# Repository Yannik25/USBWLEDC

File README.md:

# USBWLEDC
USB Sound Reactive WLED Controller

## Features

- USB-C for flashing and power (max. 3A)
- Small size (30mm x 35mm)
- Cheap components
- GSA4737 MEMS Microphone (similar to SPM1423)
- Solder Pads instead of Screw Terminal Blocks
- Files for panelized version (4x4)
- Files for 3D printed case
- Front side can be populated by JLCPCB

## Case

## Entering Flash Mode

To enter the Flash mode of the USBWLEDC, simply hold down the button as you connect the USB cable to a computer.

\* Update: With Rev. 1.2, CH340C has auto reset functionality, there should be no need to press the button during connection. 

## WLED Config

| Name | Value |
|------|-------|
| LED Output 1: GPIO | 32 |
| LED Output 2: GPIO | 33 |
| Button 0: GPIO | 0 |
| Digitalmic: Type | Generic I2S PDM |
| Digitalmic: Pin I2S SD | GPIO 23 |
| Digitalmic: Pin I2S WS | GPIO 22 |

## BOM

|Designators   |Footprint                                       |Quantity|Value                  |LCSC Part #|
|--------------|------------------------------------------------|--------|-----------------------|-----------|
|C1*, C2, C4, C9, C10 |Capacitor_SMD:C_0402_1005Metric                           |5    |100nF                  |C1525  |
|C3, C5, C7 |Capacitor_SMD:C_0603_1608Metric                           |3    |10uF                   |C96446  |
|C6         |Capacitor_SMD:C_0402_1005Metric                           |1    |1uF                    |C52923  |
|C8         |Capacitor_SMD:CP_Elec_5x5.4                               |1    |100uF                  |C7469983 |
|J10        |Connector_USB:USB_C_Receptacle_G-Switch_GT-USB-7010ASV    |1    |USB-C Receptacle       |C2988369|
|MK1*       |Microphone:Microphone-6pin                                |1    |ICS-43434 MEMS Microphone|C5656610|
|R1*        |Resistor_SMD:R_0402_1005Metric                            |1    |100k                   |C25741  |
|R2, R3, R6, R7    |Resistor_SMD:R_0402_1005Metric                            |4    |10k                    |C25531  |
|R4, R5     |Resistor_SMD:R_0603_1608Metric                            |2    |5.1k                   |C23186  |
|SW1        |Button_Switch_SMD:SW_Push_1P1T_XKB_TS-1187A               |1    |Push Button Flash      |C318884 |
|U2         |Package_TO_SOT_SMD:SOT-223-3_TabPin2                      |1    |AMS1117-3.3            |C6186   |
|U3**       |RF_Module:ESP32-WROOM-32E                                  |1    |ESP32-WROOM-32E         |C701341 |
|U4 		|Package_SO:VSSOP-8_2.3x2mm_P0.5mm			|1 		|SN74LVC2T45DCUR 		|C15741 |
|U5 		|Package_SO:SOIC-16_3.9x9.9mm_P1.27mm		|1 		|CH340C 				|C84681  |
|Q1, Q2       |Package_TO_SOT_SMD:SOT-23                                |2    |L8050QLT1G        |C49581 |
|D1       |Package_TO_SOT_SMD:SOT-143                               |1    |SP0503BAHT        |C2682275 |

\* You can build it without the microphone. Then you don't need R1, C1 and MK1.

\*\* The ESP32-WROOM Module can be purchased at a lower cost on AliExpress.

## Assembly

When ordering from JLCPCB, you have the option to get the front side of the board pre-populated - A service I strongly endorse. Subsequently, you'll only need to solder the ESP32-WROOM module onto the reverse side. With sufficient flux, this task can be accomplished with relative ease.

For those looking to populate the whole board, I suggest using a hot plate or a reflow oven for the front side.

    Be careful to keep Isopropyl Alcohol away from the hole of the microphone when cleaning the board!

## Disclaimer

The circuit board provided on this GitHub repository is offered "as is," without any warranties or guarantees of any kind. By accessing and utilizing this circuit board, you acknowledge and agree that you do so at your own risk.

The creator and contributor of this repository, shall not be held responsible or liable for any damages, losses, or injuries that may occur as a result of building and / or using this circuit board. This includes but is not limited to any direct, indirect, consequential, or incidental damages.

Electricity is dangerous. Only attempt this project if you know what you're doing.

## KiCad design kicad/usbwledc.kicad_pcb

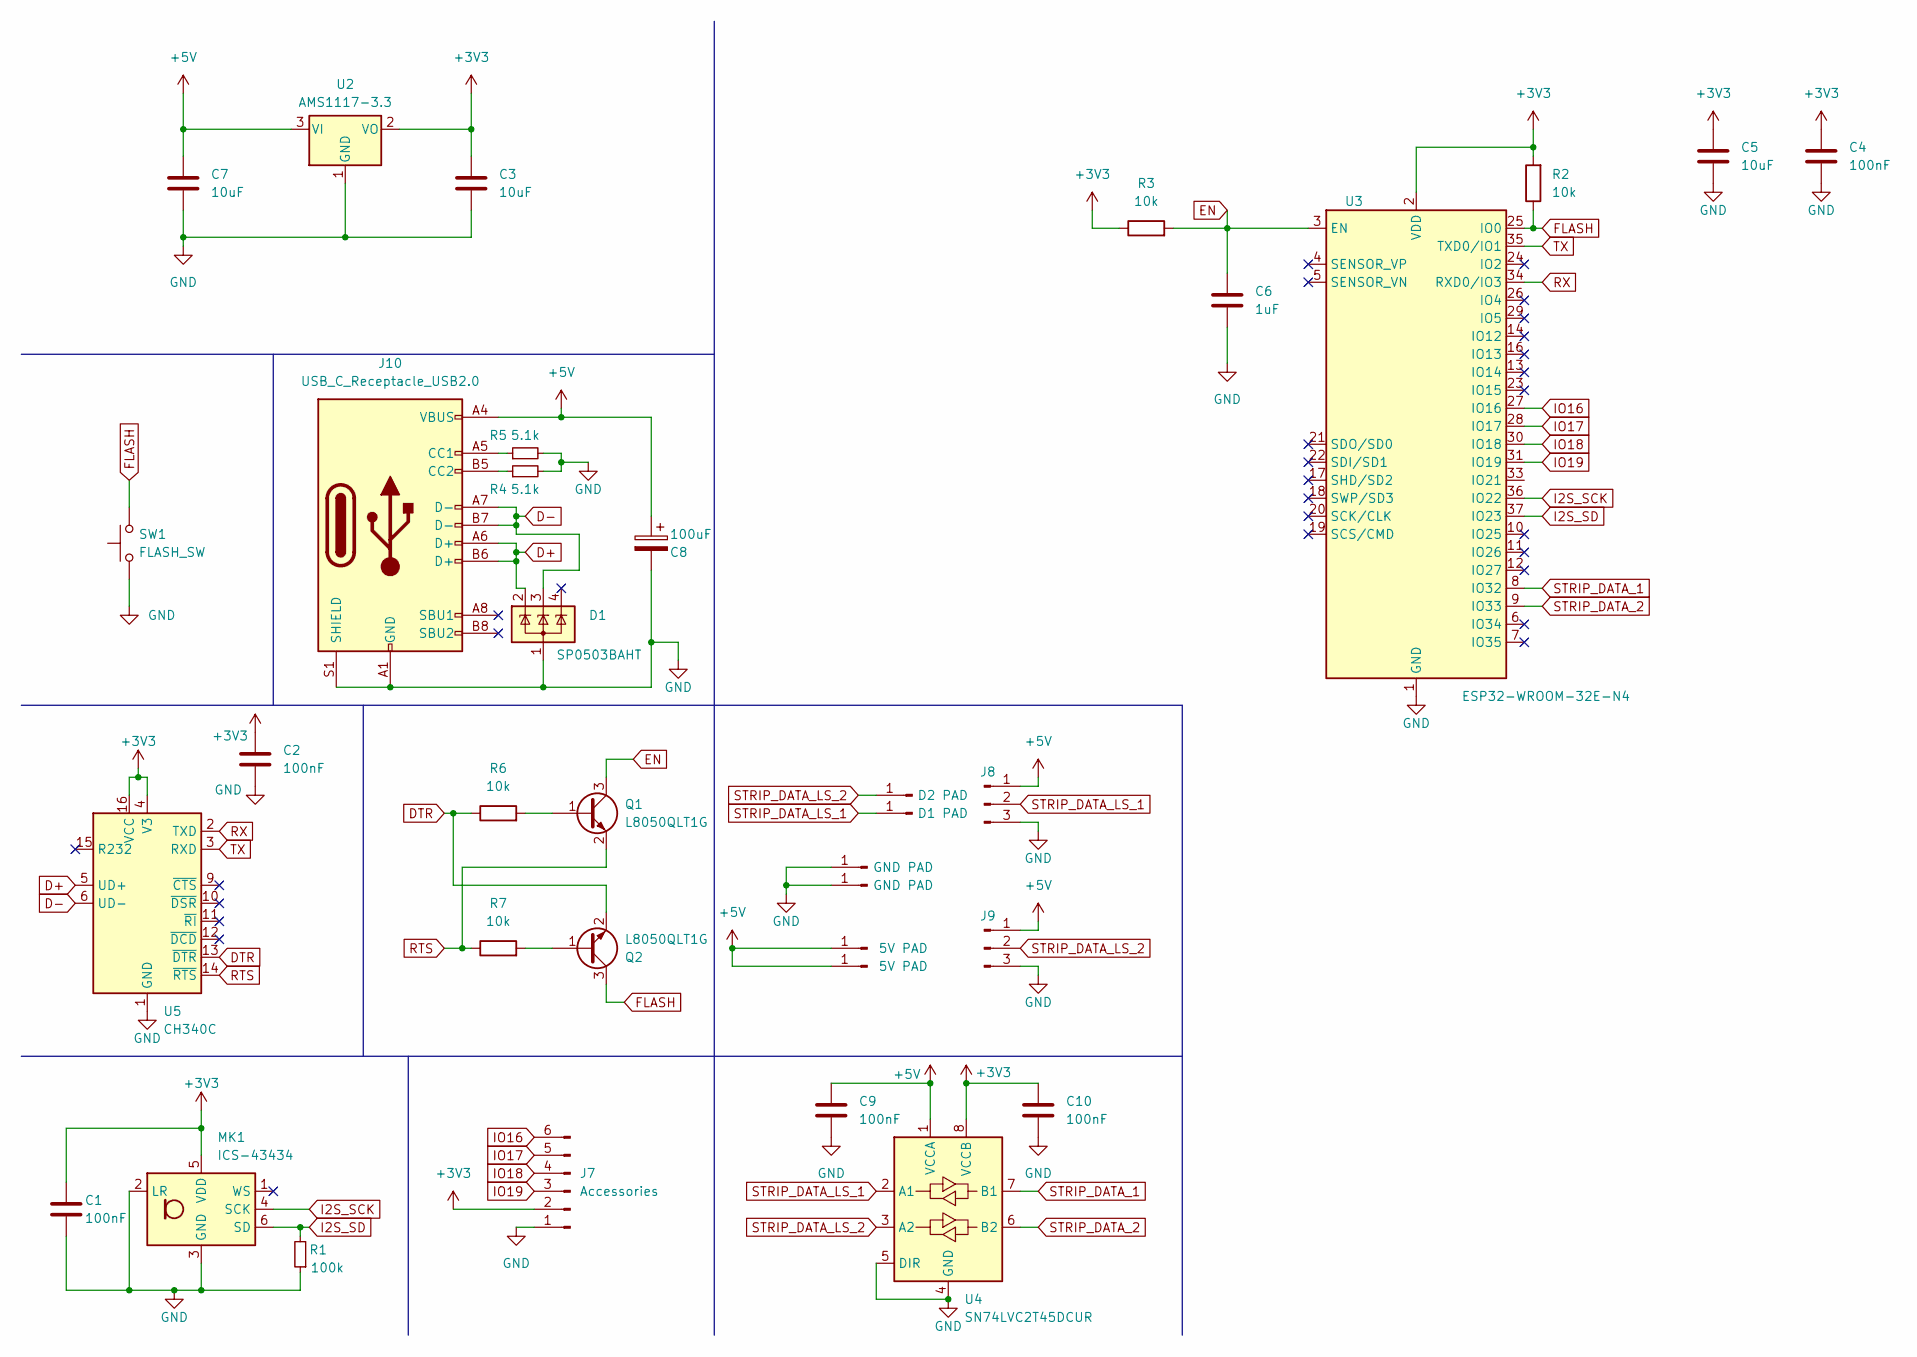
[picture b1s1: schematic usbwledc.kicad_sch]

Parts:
C1, C2, C4, C9, C10: 100nF; C_0402_1005Metric; MPN C1525; LCSC C1525
C3, C5, C7: 10uF; C_0603_1608Metric; MPN C96446; LCSC C96446
C6: 1uF; C_0402_1005Metric; MPN C52923; LCSC C52923
C8: 100uF; CP_Elec_5x5.4; MPN C7469983; LCSC C7469983
D1: SP0503BAHT; SOT-143; MPN C2682275; LCSC C2682275
J1, J4: 5V PAD; SolderWirePad_1x01_SMD_3x6mm
J2: D1 PAD; SolderWirePad_1x01_SMD_3x6mm
J3, J6: GND PAD; SolderWirePad_1x01_SMD_3x6mm
J5: D2 PAD; SolderWirePad_1x01_SMD_3x6mm
J7: Accessories; PinHeader_1x06_P2.54mm_Vertical
J8, J9: Conn_01x03_Pin; PinHeader_1x03_P2.54mm_Vertical
J10: USB_C_Receptacle_USB2.0; USB_C_Receptacle_G-Switch_GT-USB-7010ASV; MPN C2988369; LCSC C2988369
MK1: ICS-43434; InvenSense_ICS-43434-6_3.5x2.65mm; LCSC C5656610
Q1, Q2: L8050QLT1G; SOT-23; MPN C49581; LCSC C49581
R1: 100k; R_0402_1005Metric; MPN C25741; LCSC C25741
R2, R3, R6, R7: 10k; R_0402_1005Metric; MPN C25531; LCSC C25531
R4, R5: 5.1k; R_0603_1608Metric; MPN C23186; LCSC C23186
SW1: FLASH_SW; SW_Push_1P1T_XKB_TS-1187A; MPN C318884; LCSC C318884
U2: AMS1117-3.3; SOT-223-3_TabPin2; MPN C6186; LCSC C6186
U3: ESP32-WROOM-32E-N4; ESP32-WROOM-32E; MPN C701341; LCSC C701341
U4: SN74LVC2T45DCUR; VSSOP-8_2.3x2mm_P0.5mm; LCSC C15741
U5: CH340C; SOIC-16_3.9x9.9mm_P1.27mm; LCSC C84681

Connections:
+3V3: C1.1, C2.2, C3.1, C4.2, C5.1, C10.1, J7.2, MK1.5 (VDD), R2.2, R3.1, U2.2 (VO), U3.2 (VDD), U4.8 (VCCB), U5.4 (V3), U5.16 (VCC)
+5V: C7.1, C8.1, C9.1, J1.1, J4.1, J8.1, J9.1, J10.A4 (VBUS), J10.A9 (VBUS), J10.B4 (VBUS), J10.B9 (VBUS), U2.3 (VI), U4.1 (VCCA)
D+: D1.2 (K), J10.A6 (D+), J10.B6 (D+), U5.5 (UD+)
D-: D1.3 (K), J10.A7 (D-), J10.B7 (D-), U5.6 (UD-)
DTR: Q2.2 (E), R6.1, U5.13 (~DTR)
EN: C6.1, Q1.3 (C), R3.2, U3.3 (EN)
FLASH: Q2.3 (C), R2.1, SW1.2, U3.25 (IO0)
GND: C1.2, C2.1, C3.2, C4.1, C5.2, C6.2, C7.2, C8.2, C9.2, C10.2, D1.1 (A), J3.1, J6.1, J7.1, J8.3, J9.3, J10.A1 (GND), J10.A12 (GND), J10.B1 (GND), J10.B12 (GND), J10.S1 (SHIELD), MK1.2 (LR), MK1.3 (GND), R1.1, R4.2, R5.2, SW1.1, U2.1 (GND), U3.1 (GND), U3.15 (GND), U3.38 (GND), U3.39 (GND), U4.4 (GND), U4.5 (DIR), U5.1 (GND)
I2S_SCK: MK1.4 (SCK), U3.36 (IO22)
I2S_SD: MK1.6 (SD), R1.2, U3.37 (IO23)
IO16: J7.6, U3.27 (IO16)
IO17: J7.5, U3.28 (IO17)
IO18: J7.4, U3.30 (IO18)
IO19: J7.3, U3.31 (IO19)
unnamed: J10.A5 (CC1), R5.1
unnamed: J10.B5 (CC2), R4.1
unnamed: Q1.1 (B), R6.2
unnamed: Q2.1 (B), R7.2
RTS: Q1.2 (E), R7.1, U5.14 (~RTS)
RX: U3.34 (RXD0/IO3), U5.2 (TXD)
STRIP_DATA_1: U3.8 (IO32), U4.7 (B1)
STRIP_DATA_2: U3.9 (IO33), U4.6 (B2)
STRIP_DATA_LS_1: J2.1, J8.2, U4.2 (A1)
STRIP_DATA_LS_2: J5.1, J9.2, U4.3 (A2)
TX: U3.35 (TXD0/IO1), U5.3 (RXD)

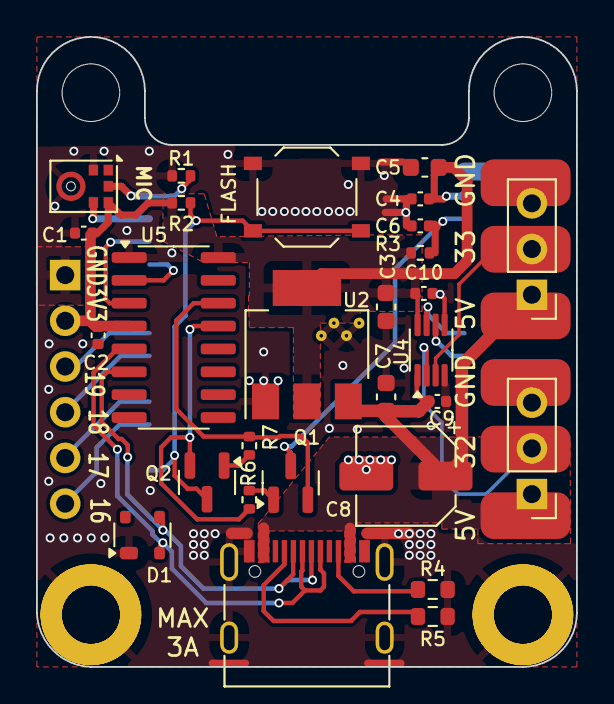
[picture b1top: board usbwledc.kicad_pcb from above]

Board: 2 copper layers, 30.0 x 35.0 mm, 40 parts (1 on the bottom side), 25 nets.

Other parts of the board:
H1, H2, H3, H4: MountingHole; MountingHole_3.2mm_M3_DIN965_Pad

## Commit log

2024-12-23 update to Revision 1.2
    Updated:
    ESP32-WROOM-32 to ESP32-WROOM-32E
    Changed CH340N to CH340C with Auto reset function
    Changed components from 0805 to 0603/0402
    Updated JLCPC component C8 to C7469983
    Added:
2024-12-23 Update README.md
    correct component count
2025-01-12 fix resistor placement instead of caps, replace mic, fix count of components
